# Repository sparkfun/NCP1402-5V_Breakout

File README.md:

NCP1402-5V Step-Up Breakout
===================

[
*NCP1402- 5V Step-Up Breakout (PRT-10968)*](https://www.sparkfun.com/products/10968)

The NCP1402 breakout board accepts input voltages between 1 and 4 Volts. 
It outputs a constant, low ripple 5V output capable of sourcing up to 200 mA. 

Repository Contents
-------------------

* **/Hardware** - All Eagle design files (.brd, .sch, .STL)
* **/Production** - Test bed files and production panel files

License Information
-------------------
The hardware is released under [Creative Commons ShareAlike 4.0 International](https://creativecommons.org/licenses/by-sa/4.0/).

Distributed as-is; no warranty is given.

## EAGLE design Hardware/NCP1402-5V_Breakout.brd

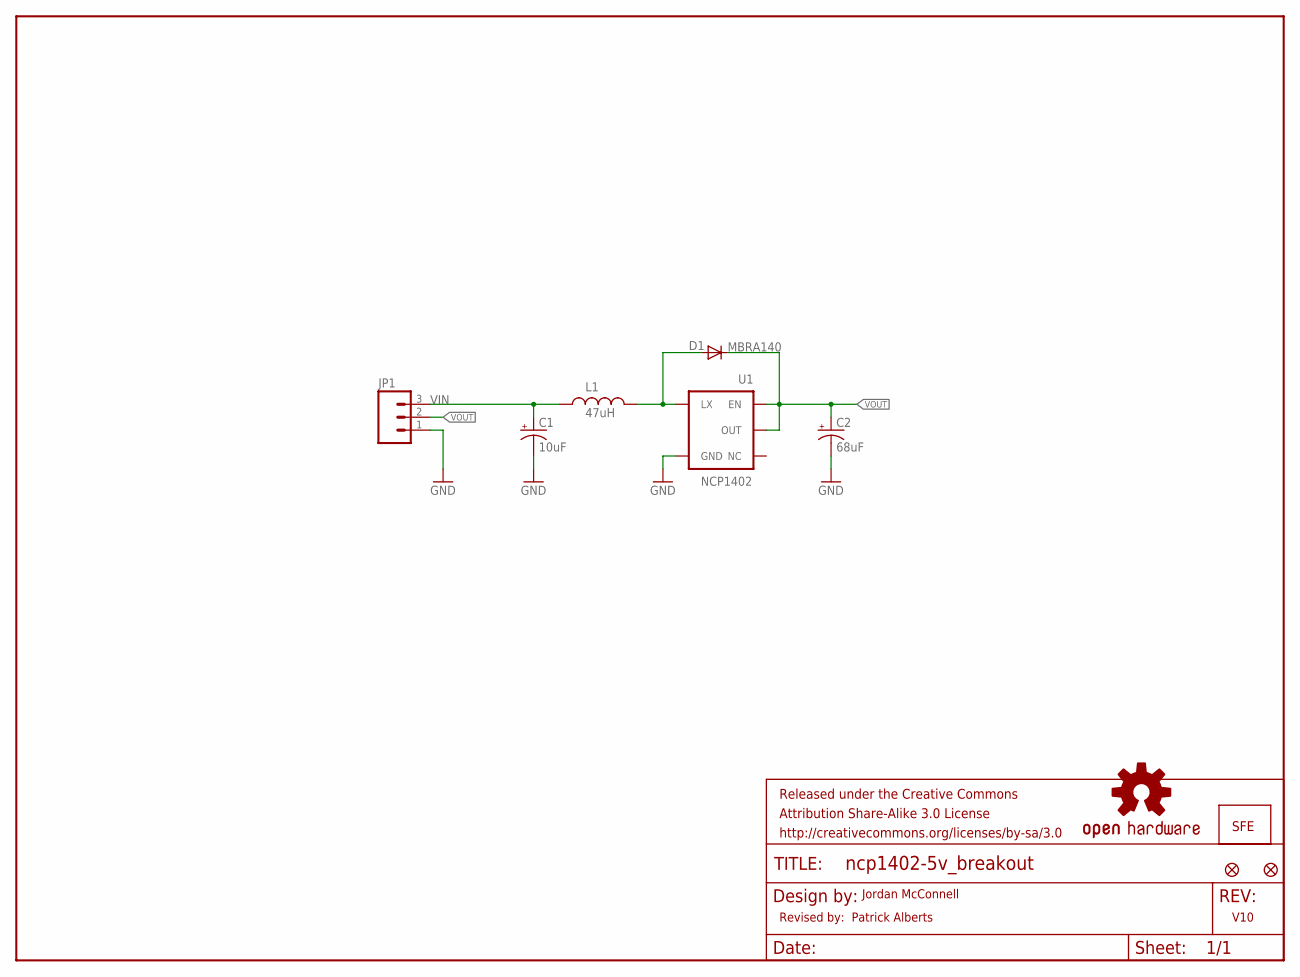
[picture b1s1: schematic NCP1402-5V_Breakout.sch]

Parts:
C1: 10uF; EIA3216
C2: 68uF; EIA3528
D1: MBRA140; SMA-DIODE
FID1, FID2: FIDUCIAL1X2; FIDUCIAL-1X2
FRAME1: FRAME-LETTER; CREATIVE_COMMONS
JP1: M03PTH; 1X03
JP2: LOGO-SFESK; SFE-LOGO-FLAME
L1: 47uH; CR54
U1: NCP1402; SOT23-5
U$1: OSHW-LOGOS; OSHW-LOGO-S

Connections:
GND: C1.C (-), C2.C (-), JP1.1, U1.4 (GND)
unnamed: D1.A, L1.P$2 (2), U1.5 (LX)
VIN: C1.A (+), JP1.3, L1.P$1 (1)
VOUT: C2.A (+), D1.C, JP1.2, U1.1 (EN), U1.2 (OUT)

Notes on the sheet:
V10
Jordan McConnell
Revised by: Patrick Alberts

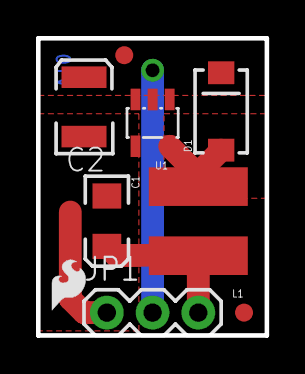
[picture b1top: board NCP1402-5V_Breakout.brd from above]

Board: 2 copper layers, 12.7 x 16.5 mm, 11 parts (1 on the bottom side), 4 nets.

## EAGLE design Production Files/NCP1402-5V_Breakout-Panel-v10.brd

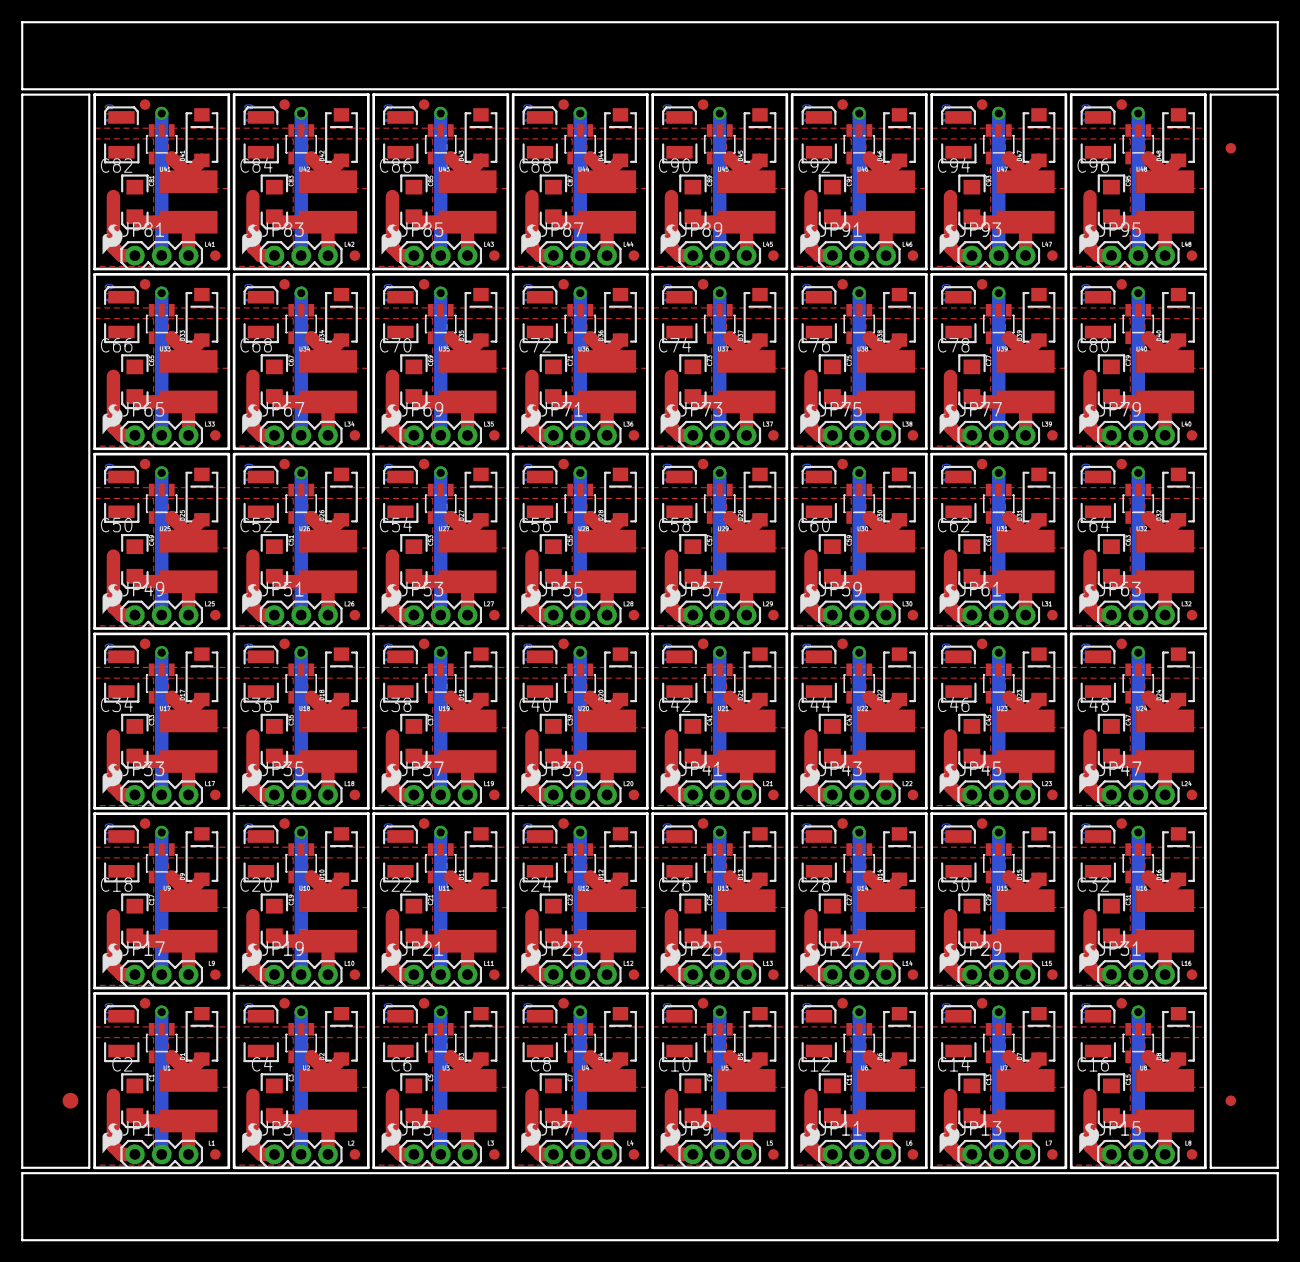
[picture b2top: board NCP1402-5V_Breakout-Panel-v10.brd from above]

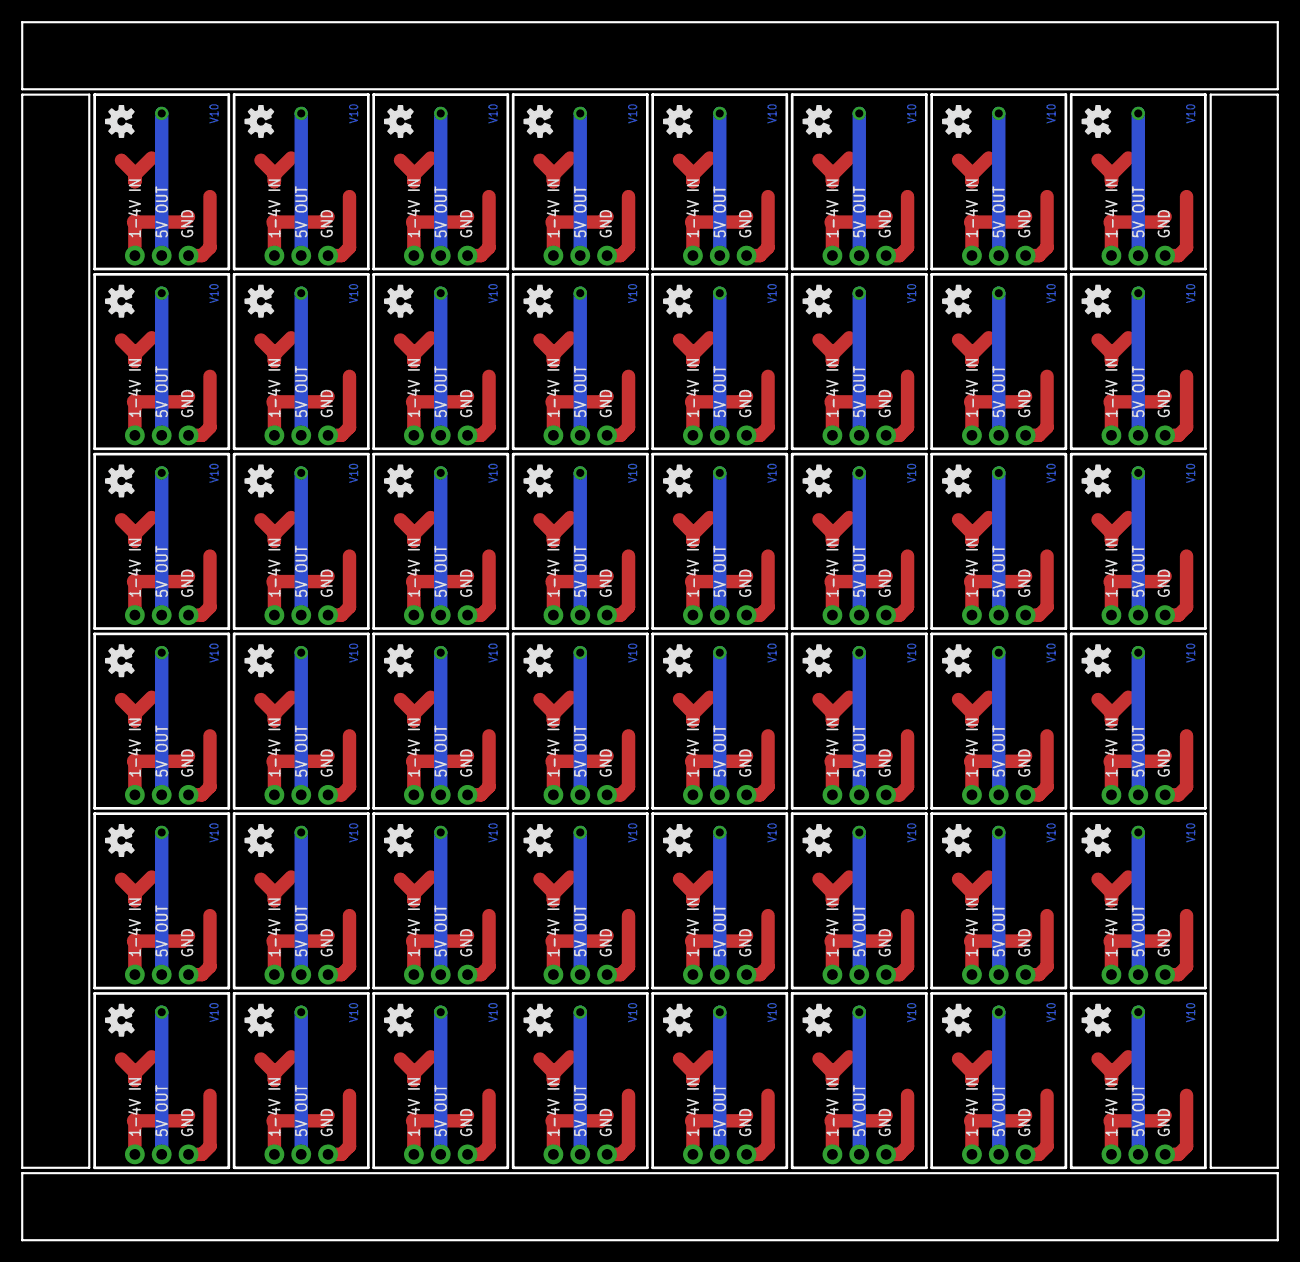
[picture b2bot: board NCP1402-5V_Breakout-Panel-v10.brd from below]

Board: 2 copper layers, 118.8 x 115.3 mm, 483 parts (48 on the bottom side), 192 nets.

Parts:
C1, C3, C5, C7, C9, C11, C13, C15, C17, C19, C21, C23, C25, C27, C29, C31, C33, C35, C37, C39, C41, C43, C45, C47, C49, C51, C53, C55, C57, C59, C61, C63, C65, C67, C69, C71, C73, C75, C77, C79, C81, C83, C85, C87, C89, C91, C93, C95: 10uF; EIA3216
C2, C4, C6, C8, C10, C12, C14, C16, C18, C20, C22, C24, C26, C28, C30, C32, C34, C36, C38, C40, C42, C44, C46, C48, C50, C52, C54, C56, C58, C60, C62, C64, C66, C68, C70, C72, C74, C76, C78, C80, C82, C84, C86, C88, C90, C92, C94, C96: 68uF; EIA3528
D1, D2, D3, D4, D5, D6, D7, D8, D9, D10, D11, D12, D13, D14, D15, D16, D17, D18, D19, D20, D21, D22, D23, D24, D25, D26, D27, D28, D29, D30, D31, D32, D33, D34, D35, D36, D37, D38, D39, D40, D41, D42, D43, D44, D45, D46, D47, D48: MBRA140; SMA-DIODE
E$1: FIDUCIAL-1.5X3
E$4, E$5: FIDUCIAL-1X2
FID1, FID2, FID3, FID4, FID5, FID6, FID7, FID8, FID9, FID10, FID11, FID12, FID13, FID14, FID15, FID16, FID17, FID18, FID19, FID20, FID21, FID22, FID23, FID24, FID25, FID26, FID27, FID28, FID29, FID30, FID31, FID32, FID33, FID34, FID35, FID36, FID37, FID38, FID39, FID40, FID41, FID42, FID43, FID44, FID45, FID46, FID47, FID48, FID49, FID50, FID51, FID52, FID53, FID54, FID55, FID56, FID57, FID58, FID59, FID60, FID61, FID62, FID63, FID64, FID65, FID66, FID67, FID68, FID69, FID70, FID71, FID72, FID73, FID74, FID75, FID76, FID77, FID78, FID79, FID80, FID81, FID82, FID83, FID84, FID85, FID86, FID87, FID88, FID89, FID90, FID91, FID92, FID93, FID94, FID95, FID96: FIDUCIAL1X2; FIDUCIAL-1X2
JP1, JP3, JP5, JP7, JP9, JP11, JP13, JP15, JP17, JP19, JP21, JP23, JP25, JP27, JP29, JP31, JP33, JP35, JP37, JP39, JP41, JP43, JP45, JP47, JP49, JP51, JP53, JP55, JP57, JP59, JP61, JP63, JP65, JP67, JP69, JP71, JP73, JP75, JP77, JP79, JP81, JP83, JP85, JP87, JP89, JP91, JP93, JP95: 1X03
JP2, JP4, JP6, JP8, JP10, JP12, JP14, JP16, JP18, JP20, JP22, JP24, JP26, JP28, JP30, JP32, JP34, JP36, JP38, JP40, JP42, JP44, JP46, JP48, JP50, JP52, JP54, JP56, JP58, JP60, JP62, JP64, JP66, JP68, JP70, JP72, JP74, JP76, JP78, JP80, JP82, JP84, JP86, JP88, JP90, JP92, JP94, JP96: LOGO-SFESK; SFE-LOGO-FLAME
L1, L2, L3, L4, L5, L6, L7, L8, L9, L10, L11, L12, L13, L14, L15, L16, L17, L18, L19, L20, L21, L22, L23, L24, L25, L26, L27, L28, L29, L30, L31, L32, L33, L34, L35, L36, L37, L38, L39, L40, L41, L42, L43, L44, L45, L46, L47, L48: 47uH; CR54
U1, U2, U3, U4, U5, U6, U7, U8, U9, U10, U11, U12, U13, U14, U15, U16, U17, U18, U19, U20, U21, U22, U23, U24, U25, U26, U27, U28, U29, U30, U31, U32, U33, U34, U35, U36, U37, U38, U39, U40, U41, U42, U43, U44, U45, U46, U47, U48: NCP1402; SOT23-5
U$1, U$2, U$3, U$4, U$5, U$6, U$7, U$8, U$9, U$10, U$11, U$12, U$13, U$14, U$15, U$16, U$17, U$18, U$19, U$20, U$21, U$22, U$23, U$24, U$25, U$26, U$27, U$28, U$29, U$30, U$31, U$32, U$33, U$34, U$35, U$36, U$37, U$38, U$39, U$40, U$41, U$42, U$43, U$44, U$45, U$46, U$47, U$48: OSHW-LOGOS; OSHW-LOGO-S

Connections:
GND: C1.C, C2.C, JP1.1, U1.4
GND1: C3.C, C4.C, JP3.1, U2.4
GND2: C5.C, C6.C, JP5.1, U3.4
GND3: C7.C, C8.C, JP7.1, U4.4
GND4: C9.C, C10.C, JP9.1, U5.4
GND5: C11.C, C12.C, JP11.1, U6.4
GND6: C13.C, C14.C, JP13.1, U7.4
GND7: C15.C, C16.C, JP15.1, U8.4
GND8: C17.C, C18.C, JP17.1, U9.4
GND9: C19.C, C20.C, JP19.1, U10.4
GND10: C21.C, C22.C, JP21.1, U11.4
GND11: C23.C, C24.C, JP23.1, U12.4
GND12: C25.C, C26.C, JP25.1, U13.4
GND13: C27.C, C28.C, JP27.1, U14.4
GND14: C29.C, C30.C, JP29.1, U15.4
GND15: C31.C, C32.C, JP31.1, U16.4
GND16: C33.C, C34.C, JP33.1, U17.4
GND17: C35.C, C36.C, JP35.1, U18.4
GND18: C37.C, C38.C, JP37.1, U19.4
GND19: C39.C, C40.C, JP39.1, U20.4
GND20: C41.C, C42.C, JP41.1, U21.4
GND21: C43.C, C44.C, JP43.1, U22.4
GND22: C45.C, C46.C, JP45.1, U23.4
GND23: C47.C, C48.C, JP47.1, U24.4
GND24: C49.C, C50.C, JP49.1, U25.4
GND25: C51.C, C52.C, JP51.1, U26.4
GND26: C53.C, C54.C, JP53.1, U27.4
GND27: C55.C, C56.C, JP55.1, U28.4
GND28: C57.C, C58.C, JP57.1, U29.4
GND29: C59.C, C60.C, JP59.1, U30.4
GND30: C61.C, C62.C, JP61.1, U31.4
GND31: C63.C, C64.C, JP63.1, U32.4
GND32: C65.C, C66.C, JP65.1, U33.4
GND33: C67.C, C68.C, JP67.1, U34.4
GND34: C69.C, C70.C, JP69.1, U35.4
GND35: C71.C, C72.C, JP71.1, U36.4
GND36: C73.C, C74.C, JP73.1, U37.4
GND37: C75.C, C76.C, JP75.1, U38.4
GND38: C77.C, C78.C, JP77.1, U39.4
GND39: C79.C, C80.C, JP79.1, U40.4
GND40: C81.C, C82.C, JP81.1, U41.4
GND41: C83.C, C84.C, JP83.1, U42.4
GND42: C85.C, C86.C, JP85.1, U43.4
GND43: C87.C, C88.C, JP87.1, U44.4
GND44: C89.C, C90.C, JP89.1, U45.4
GND45: C91.C, C92.C, JP91.1, U46.4
GND46: C93.C, C94.C, JP93.1, U47.4
GND47: C95.C, C96.C, JP95.1, U48.4
unnamed: D2.A, L2.P$2, U2.5
unnamed: D3.A, L3.P$2, U3.5
unnamed: D1.A, L1.P$2, U1.5
unnamed: D4.A, L4.P$2, U4.5
unnamed: D5.A, L5.P$2, U5.5
unnamed: D6.A, L6.P$2, U6.5
unnamed: D7.A, L7.P$2, U7.5
unnamed: D8.A, L8.P$2, U8.5
unnamed: D9.A, L9.P$2, U9.5
unnamed: D10.A, L10.P$2, U10.5
unnamed: D11.A, L11.P$2, U11.5
unnamed: D12.A, L12.P$2, U12.5
unnamed: D13.A, L13.P$2, U13.5
unnamed: D14.A, L14.P$2, U14.5
unnamed: D15.A, L15.P$2, U15.5
unnamed: D16.A, L16.P$2, U16.5
unnamed: D17.A, L17.P$2, U17.5
unnamed: D18.A, L18.P$2, U18.5
unnamed: D19.A, L19.P$2, U19.5
unnamed: D20.A, L20.P$2, U20.5
unnamed: D21.A, L21.P$2, U21.5
unnamed: D22.A, L22.P$2, U22.5
unnamed: D23.A, L23.P$2, U23.5
unnamed: D24.A, L24.P$2, U24.5
unnamed: D25.A, L25.P$2, U25.5
unnamed: D26.A, L26.P$2, U26.5
unnamed: D27.A, L27.P$2, U27.5
unnamed: D28.A, L28.P$2, U28.5
unnamed: D29.A, L29.P$2, U29.5
unnamed: D30.A, L30.P$2, U30.5
unnamed: D31.A, L31.P$2, U31.5
unnamed: D32.A, L32.P$2, U32.5
unnamed: D33.A, L33.P$2, U33.5
unnamed: D34.A, L34.P$2, U34.5
unnamed: D35.A, L35.P$2, U35.5
unnamed: D36.A, L36.P$2, U36.5
unnamed: D37.A, L37.P$2, U37.5
unnamed: D38.A, L38.P$2, U38.5
unnamed: D39.A, L39.P$2, U39.5
unnamed: D40.A, L40.P$2, U40.5
unnamed: D41.A, L41.P$2, U41.5
unnamed: D42.A, L42.P$2, U42.5
unnamed: D43.A, L43.P$2, U43.5
unnamed: D44.A, L44.P$2, U44.5
unnamed: D45.A, L45.P$2, U45.5
unnamed: D46.A, L46.P$2, U46.5
unnamed: D47.A, L47.P$2, U47.5
unnamed: D48.A, L48.P$2, U48.5
VIN: C1.A, JP1.3, L1.P$1
VIN1: C3.A, JP3.3, L2.P$1
VIN2: C5.A, JP5.3, L3.P$1
VIN3: C7.A, JP7.3, L4.P$1
VIN4: C9.A, JP9.3, L5.P$1
VIN5: C11.A, JP11.3, L6.P$1
VIN6: C13.A, JP13.3, L7.P$1
VIN7: C15.A, JP15.3, L8.P$1
VIN8: C17.A, JP17.3, L9.P$1
VIN9: C19.A, JP19.3, L10.P$1
VIN10: C21.A, JP21.3, L11.P$1
VIN11: C23.A, JP23.3, L12.P$1
VIN12: C25.A, JP25.3, L13.P$1
VIN13: C27.A, JP27.3, L14.P$1
VIN14: C29.A, JP29.3, L15.P$1
VIN15: C31.A, JP31.3, L16.P$1
VIN16: C33.A, JP33.3, L17.P$1
VIN17: C35.A, JP35.3, L18.P$1
VIN18: C37.A, JP37.3, L19.P$1
VIN19: C39.A, JP39.3, L20.P$1
VIN20: C41.A, JP41.3, L21.P$1
VIN21: C43.A, JP43.3, L22.P$1
VIN22: C45.A, JP45.3, L23.P$1
VIN23: C47.A, JP47.3, L24.P$1
VIN24: C49.A, JP49.3, L25.P$1
VIN25: C51.A, JP51.3, L26.P$1
VIN26: C53.A, JP53.3, L27.P$1
VIN27: C55.A, JP55.3, L28.P$1
VIN28: C57.A, JP57.3, L29.P$1
VIN29: C59.A, JP59.3, L30.P$1
VIN30: C61.A, JP61.3, L31.P$1
VIN31: C63.A, JP63.3, L32.P$1
VIN32: C65.A, JP65.3, L33.P$1
VIN33: C67.A, JP67.3, L34.P$1
VIN34: C69.A, JP69.3, L35.P$1
VIN35: C71.A, JP71.3, L36.P$1
VIN36: C73.A, JP73.3, L37.P$1
VIN37: C75.A, JP75.3, L38.P$1
VIN38: C77.A, JP77.3, L39.P$1
VIN39: C79.A, JP79.3, L40.P$1
VIN40: C81.A, JP81.3, L41.P$1
VIN41: C83.A, JP83.3, L42.P$1
VIN42: C85.A, JP85.3, L43.P$1
VIN43: C87.A, JP87.3, L44.P$1
VIN44: C89.A, JP89.3, L45.P$1
VIN45: C91.A, JP91.3, L46.P$1
VIN46: C93.A, JP93.3, L47.P$1
VIN47: C95.A, JP95.3, L48.P$1
VOUT: C2.A, D1.C, JP1.2, U1.1, U1.2
VOUT1: C4.A, D2.C, JP3.2, U2.1, U2.2
VOUT2: C6.A, D3.C, JP5.2, U3.1, U3.2
VOUT3: C8.A, D4.C, JP7.2, U4.1, U4.2
VOUT4: C10.A, D5.C, JP9.2, U5.1, U5.2
VOUT5: C12.A, D6.C, JP11.2, U6.1, U6.2
VOUT6: C14.A, D7.C, JP13.2, U7.1, U7.2
VOUT7: C16.A, D8.C, JP15.2, U8.1, U8.2
VOUT8: C18.A, D9.C, JP17.2, U9.1, U9.2
VOUT9: C20.A, D10.C, JP19.2, U10.1, U10.2
VOUT10: C22.A, D11.C, JP21.2, U11.1, U11.2
VOUT11: C24.A, D12.C, JP23.2, U12.1, U12.2
VOUT12: C26.A, D13.C, JP25.2, U13.1, U13.2
VOUT13: C28.A, D14.C, JP27.2, U14.1, U14.2
VOUT14: C30.A, D15.C, JP29.2, U15.1, U15.2
VOUT15: C32.A, D16.C, JP31.2, U16.1, U16.2
VOUT16: C34.A, D17.C, JP33.2, U17.1, U17.2
VOUT17: C36.A, D18.C, JP35.2, U18.1, U18.2
VOUT18: C38.A, D19.C, JP37.2, U19.1, U19.2
VOUT19: C40.A, D20.C, JP39.2, U20.1, U20.2
VOUT20: C42.A, D21.C, JP41.2, U21.1, U21.2
VOUT21: C44.A, D22.C, JP43.2, U22.1, U22.2
VOUT22: C46.A, D23.C, JP45.2, U23.1, U23.2
VOUT23: C48.A, D24.C, JP47.2, U24.1, U24.2
VOUT24: C50.A, D25.C, JP49.2, U25.1, U25.2
VOUT25: C52.A, D26.C, JP51.2, U26.1, U26.2
VOUT26: C54.A, D27.C, JP53.2, U27.1, U27.2
VOUT27: C56.A, D28.C, JP55.2, U28.1, U28.2
VOUT28: C58.A, D29.C, JP57.2, U29.1, U29.2
VOUT29: C60.A, D30.C, JP59.2, U30.1, U30.2
VOUT30: C62.A, D31.C, JP61.2, U31.1, U31.2
VOUT31: C64.A, D32.C, JP63.2, U32.1, U32.2
VOUT32: C66.A, D33.C, JP65.2, U33.1, U33.2
VOUT33: C68.A, D34.C, JP67.2, U34.1, U34.2
VOUT34: C70.A, D35.C, JP69.2, U35.1, U35.2
VOUT35: C72.A, D36.C, JP71.2, U36.1, U36.2
VOUT36: C74.A, D37.C, JP73.2, U37.1, U37.2
VOUT37: C76.A, D38.C, JP75.2, U38.1, U38.2
VOUT38: C78.A, D39.C, JP77.2, U39.1, U39.2
VOUT39: C80.A, D40.C, JP79.2, U40.1, U40.2
VOUT40: C82.A, D41.C, JP81.2, U41.1, U41.2
VOUT41: C84.A, D42.C, JP83.2, U42.1, U42.2
VOUT42: C86.A, D43.C, JP85.2, U43.1, U43.2
VOUT43: C88.A, D44.C, JP87.2, U44.1, U44.2
VOUT44: C90.A, D45.C, JP89.2, U45.1, U45.2
VOUT45: C92.A, D46.C, JP91.2, U46.1, U46.2
VOUT46: C94.A, D47.C, JP93.2, U47.1, U47.2
VOUT47: C96.A, D48.C, JP95.2, U48.1, U48.2

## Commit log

2014-01-22 Added BRD/SCH and Git
2014-02-11 Updated ann rings/sche/rev code/exposed via
    Updated the date code to version # V10, Updated to Frame Letter, Fixed
    annular ring size and fixed the exposed via
2014-02-11 changed fiducials to regular from micro
2014-02-11 created panel v10
2014-08-07 Adding product info to README

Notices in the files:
parts and their libraries:
SparkFun-Connectors: Licensing: CC v3.0 Share-Alike You are welcome to use this library for commercial purposes.
SparkFun-Aesthetics: Released under the Creative Commons Attribution Share-Alike 3.0 License
SparkFun-Aesthetics: http://creativecommons.org/licenses/by-sa/3.0
